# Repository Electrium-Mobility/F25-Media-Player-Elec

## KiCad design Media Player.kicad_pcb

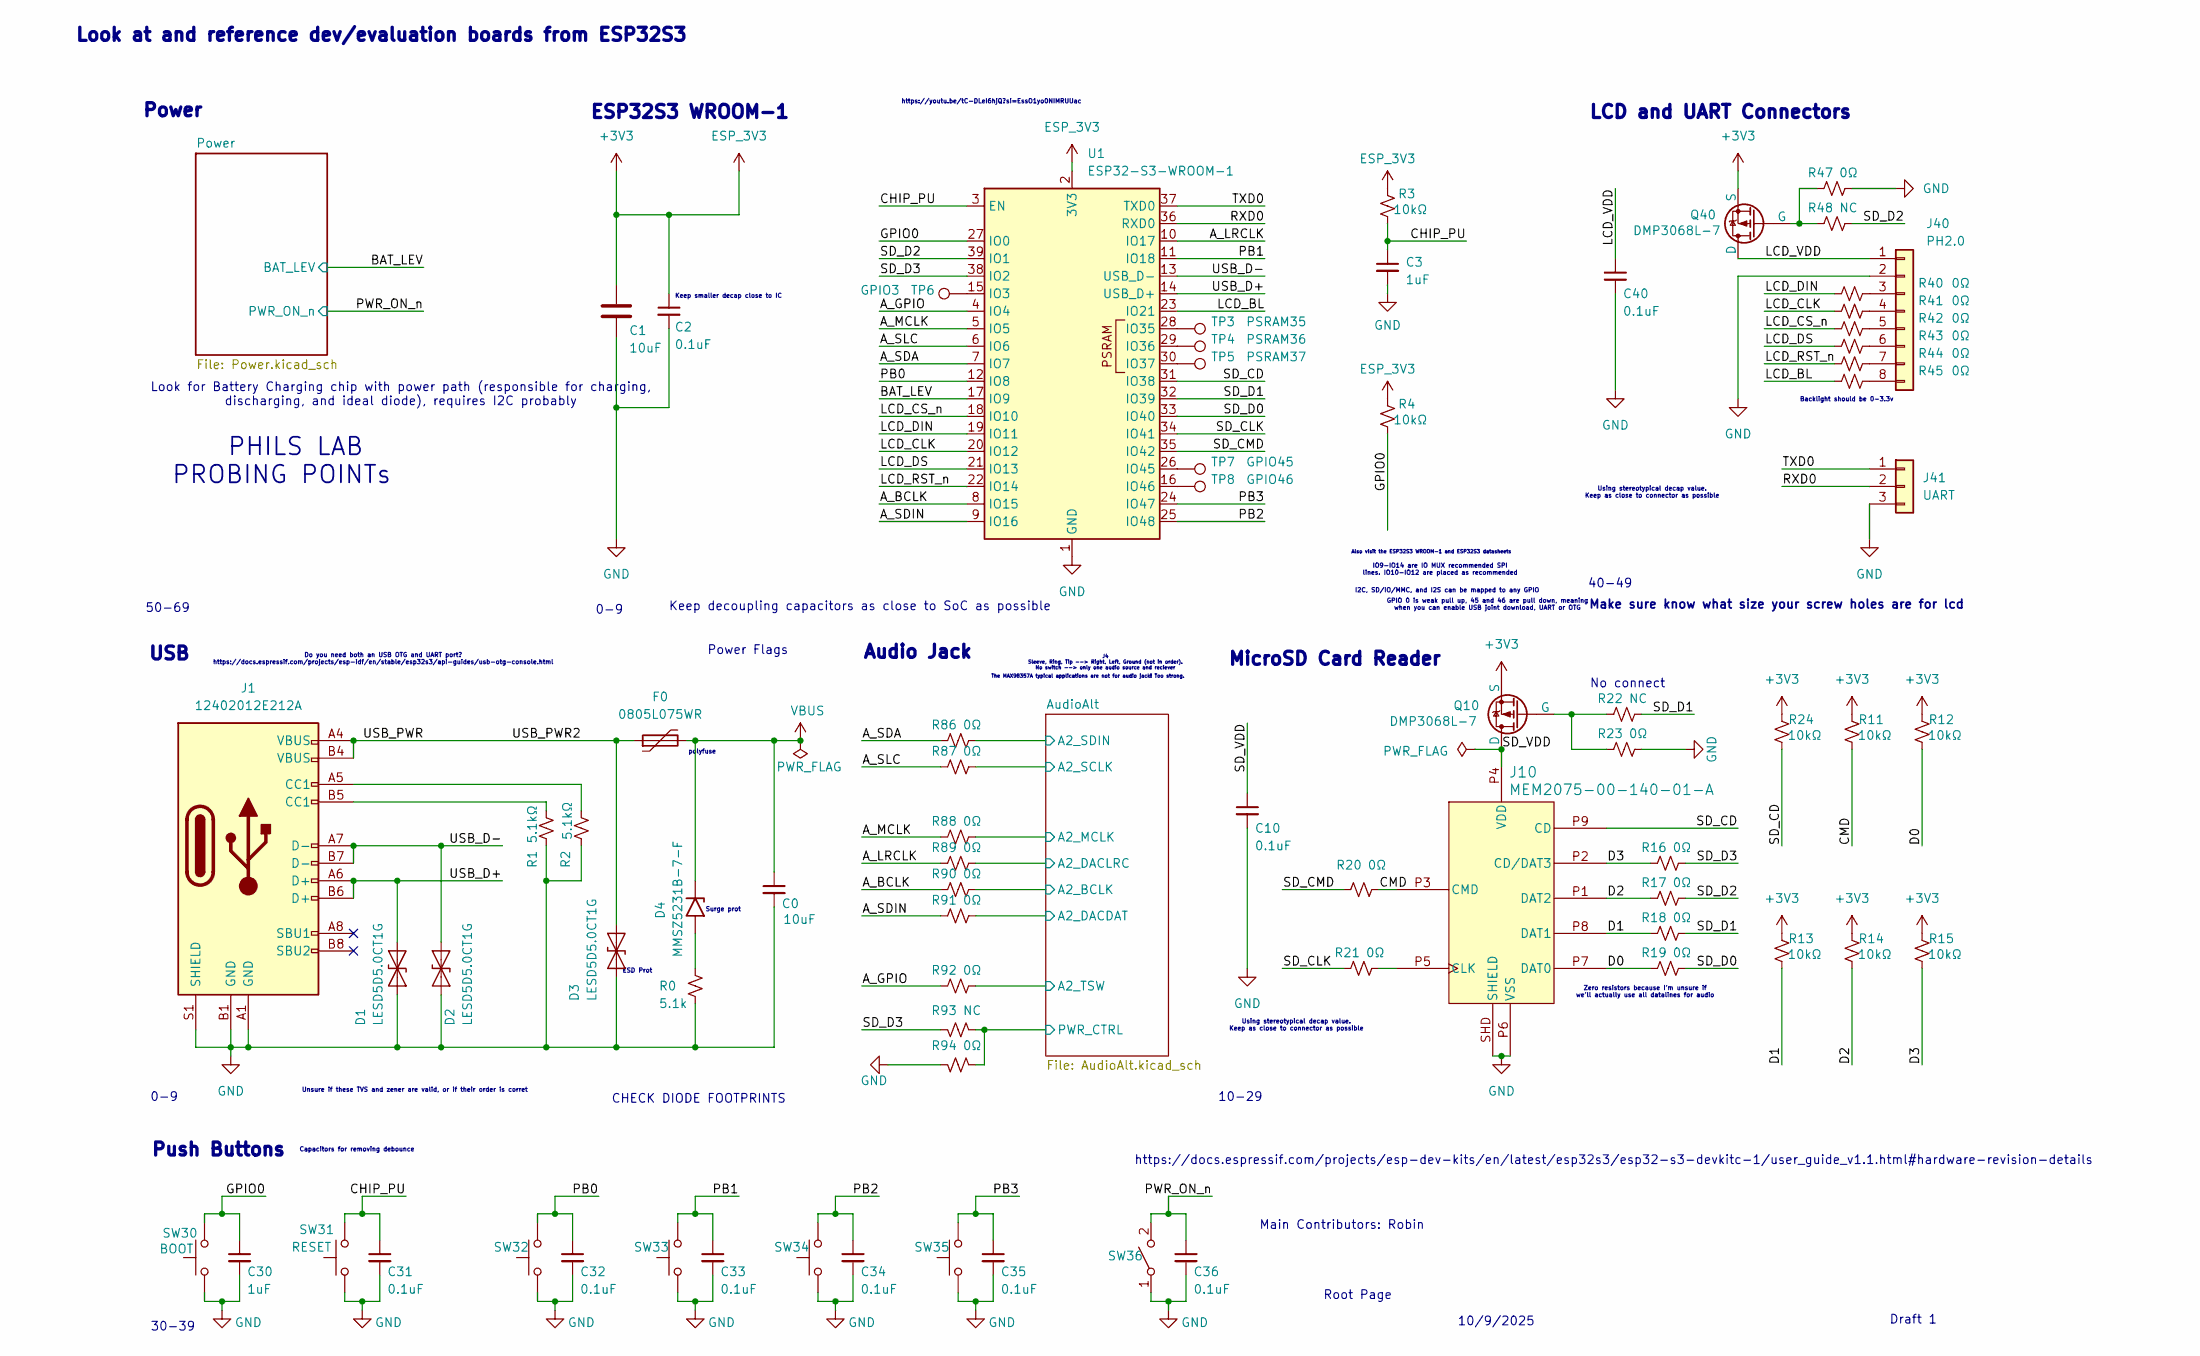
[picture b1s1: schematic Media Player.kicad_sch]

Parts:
C0: 10uF; C_0805_2012Metric_Pad1.18x1.45mm_HandSolder
C1: 10uF; C_0603_1608Metric_Pad1.08x0.95mm_HandSolder
C2, C10, C31, C32, C33, C34, C35, C36, C40: 0.1uF; C_0603_1608Metric_Pad1.08x0.95mm_HandSolder
C3, C30: 1uF; C_0603_1608Metric_Pad1.08x0.95mm_HandSolder
D1, D2, D3: LESD5D5.0CT1G; D_SOD-523
D4: MMSZ5231B-7-F; D_SOD-323
F0: 0805L075WR; D_0805_2012Metric_Pad1.15x1.40mm_HandSolder
J1: 12402012E212A; USB_C_12402012E212A_AMP
J10: MEM2075-00-140-01-A; MEM2075-00-140-01-A_GCT
J40: PH2.0; JST_EH_B8B-EH-A_1x08_P2.50mm_Vertical
J41: UART; JST_PH_B3B-PH-K_1x03_P2.00mm_Vertical
Q10, Q40: DMP3068L-7; SOT-23-3
R0: 5.1k; R_0603_1608Metric_Pad0.98x0.95mm_HandSolder
R1, R2: 5.1kΩ; R_0603_1608Metric_Pad0.98x0.95mm_HandSolder
R3, R4, R11, R12, R13, R14, R15, R24: 10kΩ; R_0603_1608Metric_Pad0.98x0.95mm_HandSolder
R16, R17, R18, R19, R20, R21, R23, R40, R41, R42, R43, R44, R45, R47, R86, R87, R88, R89, R90, R91, R92, R94: 0Ω; R_0603_1608Metric_Pad0.98x0.95mm_HandSolder
R22, R48, R93: NC; R_0603_1608Metric_Pad0.98x0.95mm_HandSolder
SW30: BOOT; SW_Push_1P1T_NO_CK_KSC6xxG
SW31: RESET; SW_Push_1P1T_NO_CK_KSC6xxG
SW32, SW33, SW34, SW35: SW_Push; SW_Push_1P1T_NO_CK_KSC6xxG
SW36: SW_SPST; SW_DIP_SPSTx01_Slide_6.7x4.1mm_W8.61mm_P2.54mm_LowProfile
TP3: PSRAM35; TestPoint_Pad_1.5x1.5mm
TP4: PSRAM36; TestPoint_Pad_1.5x1.5mm
TP5: PSRAM37; TestPoint_Pad_1.5x1.5mm
TP6: GPIO3; TestPoint_Pad_1.5x1.5mm
TP7: GPIO45; TestPoint_Pad_1.5x1.5mm
TP8: GPIO46; TestPoint_Pad_1.5x1.5mm
U1: ESP32-S3-WROOM-1

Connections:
+3V3: C1.1, C2.1, Q10.3 (S), Q40.3 (S), R3.2, R4.2, R11.2, R12.2, R13.2, R14.2, R15.2, R24.2, U1.2 (3V3); also elsewhere on the board
/A_BCLK: R90.1, U1.8 (IO15)
/A_GPIO: R92.1, U1.4 (IO4)
/A_LRCLK: R89.1, U1.10 (IO17)
/A_MCLK: R88.1, U1.5 (IO5)
/A_SDA: R86.1, U1.7 (IO7)
/A_SDIN: R91.1, U1.9 (IO16)
/A_SLC: R87.1, U1.6 (IO6)
/AudioAlt/A2_BCLK: R90.2; also elsewhere on the board
/AudioAlt/A2_DACDAT: R91.2; also elsewhere on the board
/AudioAlt/A2_DACLRC: R89.2; also elsewhere on the board
/AudioAlt/A2_MCLK: R88.2; also elsewhere on the board
/AudioAlt/A2_SCLK: R87.2; also elsewhere on the board
/AudioAlt/A2_SDIN: R86.2; also elsewhere on the board
/AudioAlt/A2_TSW: R92.2; also elsewhere on the board
/AudioAlt/PWR_CTRL: R93.1, R94.1; also elsewhere on the board
/BAT_LEV: U1.17 (IO9); also elsewhere on the board
/CHIP_PU: C3.1, C31.1, R3.1, SW31.2, U1.3 (EN)
/CMD: J10.P3 (CMD), R11.1, R20.2
/D0: J10.P7 (DAT0), R12.1, R19.1
/D1: J10.P8 (DAT1), R13.1, R18.1
/D2: J10.P1 (DAT2), R14.1, R17.1
/D3: J10.P2 (CD/DAT3), R15.1, R16.1
/GPIO0: C30.1, R4.1, SW30.2, U1.27 (IO0)
/LCD_BL: R45.1, U1.23 (IO21)
/LCD_CLK: R41.1, U1.20 (IO12)
/LCD_CS_n: R42.1, U1.18 (IO10)
/LCD_DIN: R40.1, U1.19 (IO11)
/LCD_DS: R43.1, U1.21 (IO13)
/LCD_RST_n: R44.1, U1.22 (IO14)
/LCD_VDD: C40.1, J40.1, Q40.1 (D)
/PB0: C32.1, SW32.2, U1.12 (IO8)
/PB1: C33.1, SW33.2, U1.11 (IO18)
/PB2: C34.1, SW34.2, U1.25 (IO48)
/PB3: C35.1, SW35.2, U1.24 (IO47)
/PWR_ON_n: C36.1, SW36.2 (B); also elsewhere on the board
/RXD0: J41.2, U1.36 (RXD0)
/SD_CD: J10.P9 (CD), R24.1, U1.31 (IO38)
/SD_CLK: R21.1, U1.34 (IO41)
/SD_CMD: R20.1, U1.35 (IO42)
/SD_D0: R19.2, U1.33 (IO40)
/SD_D1: R18.2, R22.2, U1.32 (IO39)
/SD_D2: R17.2, R48.2, U1.39 (IO1)
/SD_D3: R16.2, R93.2, U1.38 (IO2)
/SD_VDD: C10.1, J10.P4 (VDD), Q10.1 (D)
/TXD0: J41.1, U1.37 (TXD0)
/USB_D+: D1.1 (A1), J1.A6 (D+), J1.B6 (D+), U1.14 (USB_D+)
/USB_D-: D2.1 (A1), J1.A7 (D-), J1.B7 (D-), U1.13 (USB_D-)
/USB_PWR: D3.1 (A1), F0.1, J1.A4 (VBUS), J1.A9 (VBUS), J1.B4 (VBUS), J1.B9 (VBUS)
GND: C0.2, C1.2, C2.2, C3.2, C10.2, C30.2, C31.2, C32.2, C33.2, C34.2, C35.2, C36.2, C40.2, D1.2 (A2), D2.2 (A2), D3.2 (A2), J1.A1 (GND), J1.A12 (GND), J1.B1 (GND), J1.B12 (GND), J1.S1 (SHIELD), J10.P6 (VSS), J10.SHD (SHIELD), J40.2, J41.3, R0.2, R1.2, R2.2, R23.2, R47.2, R94.2, SW30.1, SW31.1, SW32.1, SW33.1, SW34.1, SW35.1, SW36.1 (A), U1.1 (GND), U1.40 (GND), U1.41 (GND); also elsewhere on the board
unnamed: D4.2 (A2), R0.1
unnamed: J1.A5 (CC1), R2.1
unnamed: J1.B5 (CC1), R1.1
unnamed: J10.P5 (CLK), R21.2
unnamed: J40.3, R40.2
unnamed: J40.4, R41.2
unnamed: J40.5, R42.2
unnamed: J40.6, R43.2
unnamed: J40.7, R44.2
unnamed: J40.8, R45.2
unnamed: Q10.2 (G), R22.1, R23.1
unnamed: Q40.2 (G), R47.1, R48.1
unnamed: TP6.1, U1.15 (IO3)
unnamed: TP3.1, U1.28 (IO35)
unnamed: TP4.1, U1.29 (IO36)
unnamed: TP5.1, U1.30 (IO37)
unnamed: TP7.1, U1.26 (IO45)
unnamed: TP8.1, U1.16 (IO46)
VBUS: C0.1, D4.1 (A1), F0.2; also elsewhere on the board

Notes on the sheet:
LCD and UART Connectors
Look for Battery Charging chip with power path (responsible for charging, discharging, and ideal diode), requires I2C probably
Keep decoupling capacitors as close to SoC as possible
50-69
ESP32S3 WROOM-1
Capacitors for removing debounce
Look at and reference dev/evaluation boards from ESP32S3
IO9-IO14 are IO MUX recommended SPI lines. IO10-IO12 are placed as recommended
Make sure know what size your screw holes are for lcd
GPIO 0 is weak pull up, 45 and 46 are pull down, meaning when you can enable USB joint download, UART or OTG
Push Buttons
Using stereotypical decap value. Keep as close to connector as possible
MicroSD Card Reader
Backlight should be 0-3.3v
0-9
I2C, SD/IO/MMC, and I2S can be mapped to any GPIO
Surge prot
10/9/2025
Root Page
Zero resistors because I'm unsure if we'll actually use all datalines for audio
10-29
Unsure if these TVS and zener are valid, or if their order is corret
CHECK DIODE FOOTPRINTS
Power
polyfuse
40-49
Audio Jack
30-39
Do you need both an USB OTG and UART port? https://docs.espressif.com/projects/esp-idf/en/stable/esp32s3/api-guides/usb-otg-console.html
PROBING POINTs
The MAX98357A typical applications are not for audio jack! Too strong.
Also visit the ESP32S3 WROOM-1 and ESP32S3 datasheets
Keep smaller decap close to IC
Main Contributors: Robin
No connect
PHILS LAB
Draft 1
ESD Prot
USB
https://docs.espressif.com/projects/esp-dev-kits/en/latest/esp32s3/esp32-s3-devkitc-1/user_guide_v1.1.html#hardware-revision-details

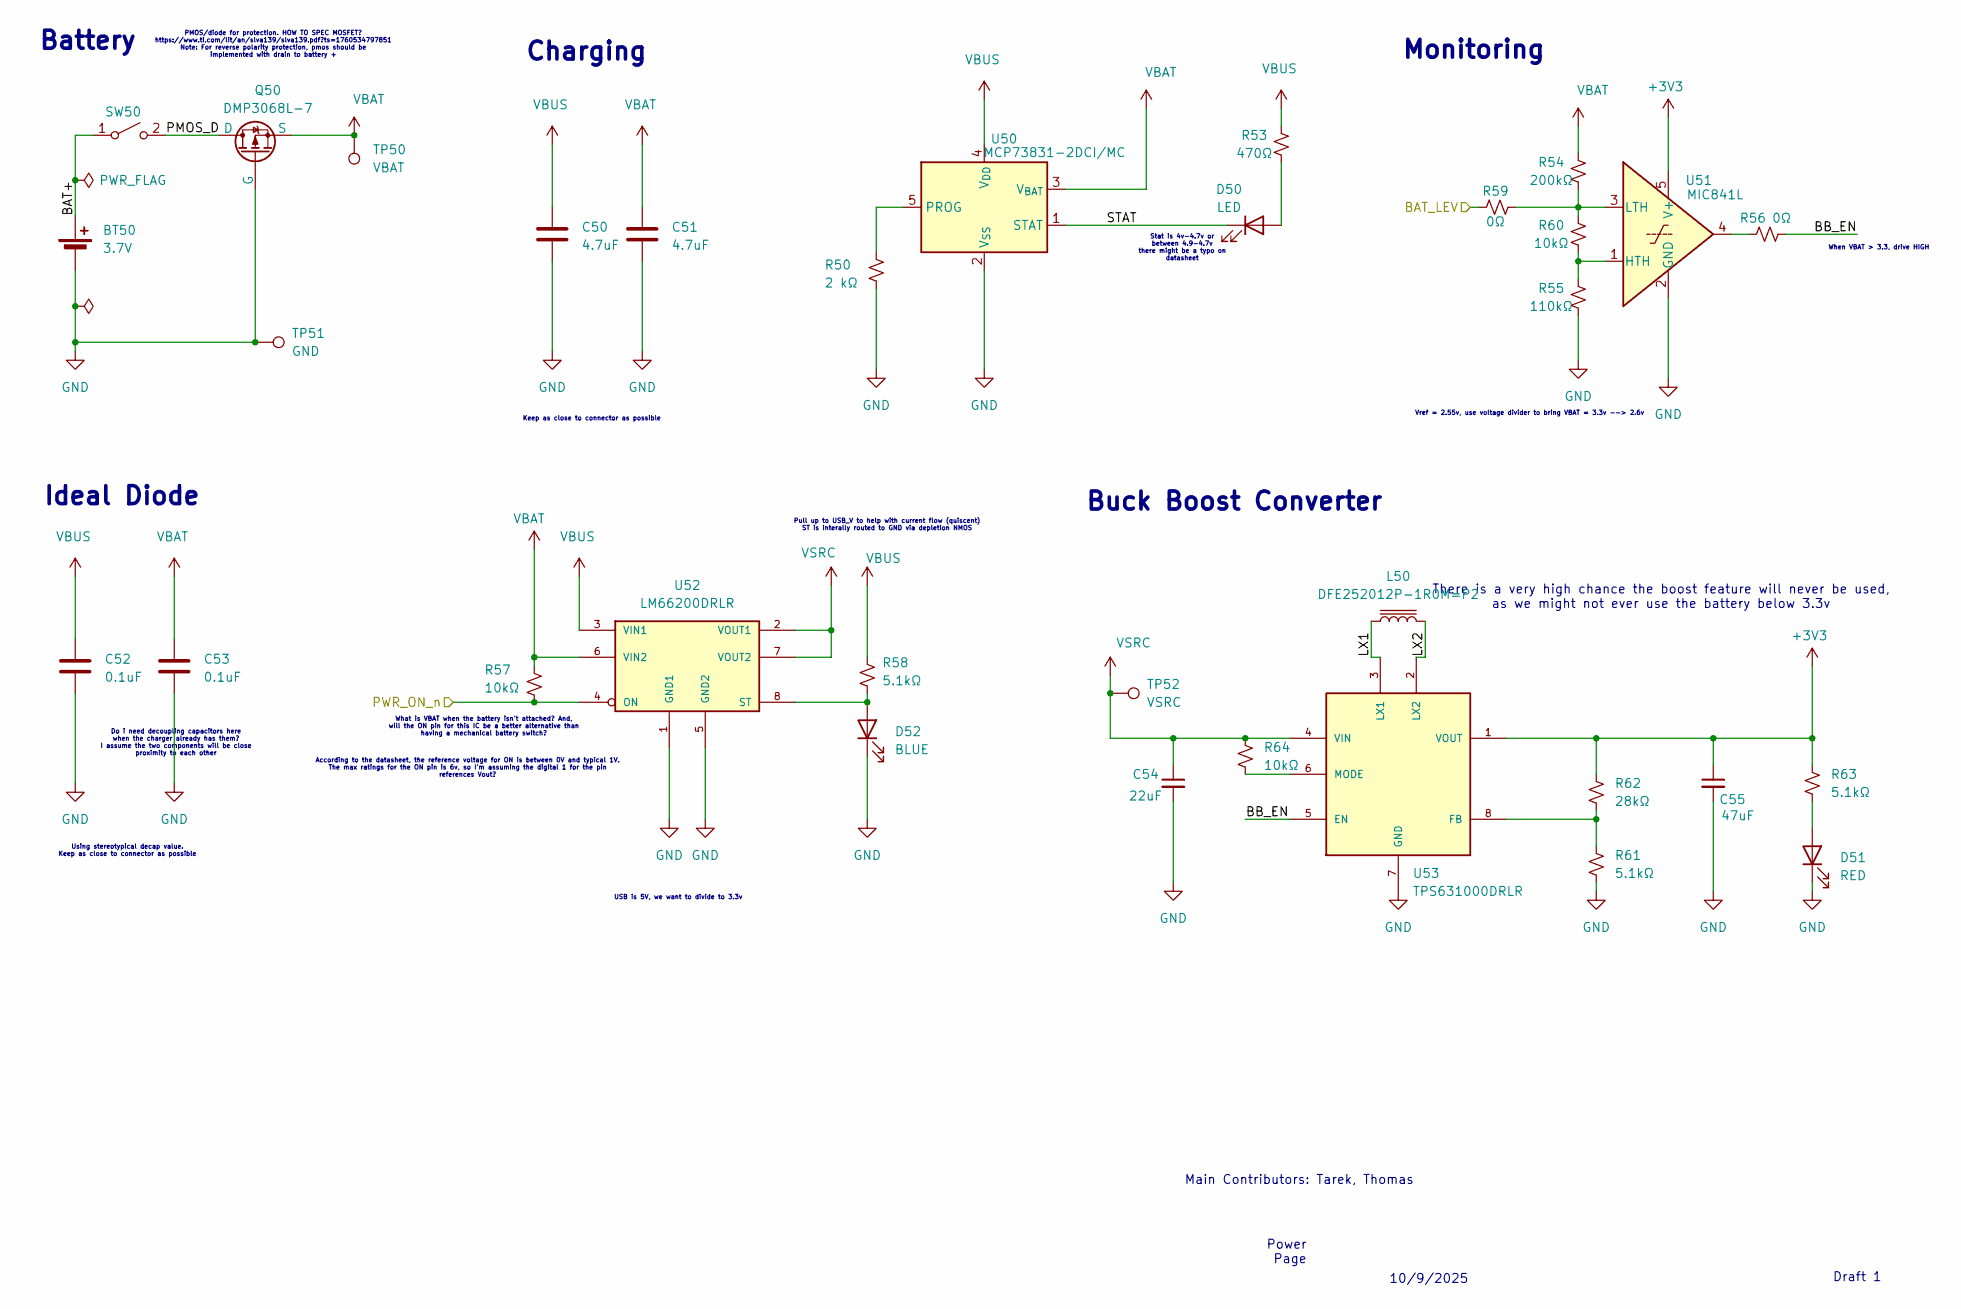
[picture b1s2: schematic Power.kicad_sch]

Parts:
BT50: 3.7V; JST_PH_B2B-PH-K_1x02_P2.00mm_Vertical
C50, C51: 4.7uF; C_0603_1608Metric_Pad1.08x0.95mm_HandSolder
C52, C53: 0.1uF; C_0603_1608Metric_Pad1.08x0.95mm_HandSolder
C54: 22uF; C_0805_2012Metric
C55: 47uF; C_0805_2012Metric
D50: LED; LED_0603_1608Metric
D51: RED; LED_0603_1608Metric
D52: BLUE; LED_0603_1608Metric
L50: DFE252012P-1R0M=P2; L_1008_2520Metric
Q50: DMP3068L-7; SOT-23-3
R50: 2 kΩ; R_0603_1608Metric_Pad0.98x0.95mm_HandSolder
R53: 470Ω; R_0603_1608Metric_Pad0.98x0.95mm_HandSolder
R54: 200kΩ; R_0603_1608Metric_Pad0.98x0.95mm_HandSolder
R55: 110kΩ; R_0603_1608Metric_Pad0.98x0.95mm_HandSolder
R56, R59: 0Ω; R_0603_1608Metric_Pad0.98x0.95mm_HandSolder
R57, R60, R64: 10kΩ; R_0603_1608Metric_Pad0.98x0.95mm_HandSolder
R58, R61, R63: 5.1kΩ; R_0603_1608Metric_Pad0.98x0.95mm_HandSolder
R62: 28kΩ; R_0603_1608Metric_Pad0.98x0.95mm_HandSolder
SW50: SW_SPST; SW_DIP_SPSTx01_Slide_6.7x4.1mm_W8.61mm_P2.54mm_LowProfile
TP50: VBAT; TestPoint_Pad_1.5x1.5mm
TP51: GND; TestPoint_THTPad_1.5x1.5mm_Drill0.7mm
TP52: VSRC; TestPoint_Pad_1.5x1.5mm
U50: MCP73831-2DCI/MC; SOT-23-5
U51: MIC841L; SOT-353_SC-70-5
U52: LM66200DRLR; SOT-583-8
U53: TPS631000DRLR; SOT-583-8; PARTREV B

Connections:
+3V3: C55.1, R62.1, R63.1, U51.5 (V+), U53.1 (VOUT); also elsewhere on the board
/BAT_LEV: R59.2; also elsewhere on the board
/PWR_ON_n: R57.2, U52.4 (ON); also elsewhere on the board
/Power/BAT+: BT50.1 (+), SW50.1 (A)
/Power/BB_EN: R56.2, U53.5 (EN)
/Power/LX1: L50.1, U53.3 (LX1)
/Power/LX2: L50.2, U53.2 (LX2)
/Power/PMOS_D: Q50.1 (D), SW50.2 (B)
/Power/STAT: D50.1 (K), U50.1 (STAT)
GND: BT50.2 (-), C50.1, C51.1, C52.1, C53.1, C54.2, C55.2, D51.1 (K), D52.1 (K), Q50.2 (G), R50.2, R55.1, R61.2, TP51.1, U50.2 (V_{SS}), U51.2 (GND), U52.1 (GND1), U52.5 (GND2), U53.7 (GND); also elsewhere on the board
unnamed: D50.2 (A), R53.1
unnamed: D51.2 (A), R63.2
unnamed: D52.2 (A), R58.2, U52.8 (ST)
unnamed: R56.1, U51.4
unnamed: R50.1, U50.5 (PROG)
unnamed: R55.2, R60.1, U51.1 (HTH)
unnamed: R54.1, R59.1, R60.2, U51.3 (LTH)
unnamed: R61.1, R62.2, U53.8 (FB)
unnamed: R64.2, U53.6 (MODE)
VBAT: C51.2, C53.2, Q50.3 (S), R54.2, R57.1, TP50.1, U50.3 (V_{BAT}), U52.6 (VIN2)
VBUS: C50.2, C52.2, R53.2, R58.1, U50.4 (V_{DD}), U52.3 (VIN1); also elsewhere on the board
VSRC: C54.1, R64.1, TP52.1, U52.2 (VOUT1), U52.7 (VOUT2), U53.4 (VIN)

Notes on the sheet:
Pull up to USB_V to help with current flow (quiscent) ST is interally routed to GND via depletion NMOS
Power Page
Vref = 2.55v, use voltage divider to bring VBAT = 3.3v --> 2.6v
Do i need decoupling capacitors here when the charger already has them? I assume the two components will be close proximity to each other
According to the datasheet, the reference voltage for ON is between 0V and typical 1V. The max ratings for the ON pin is 6v, so I'm assuming the digital 1 for the pin references Vout?
What is VBAT when the battery isn't attached? And, will the ON pin for this IC be a better alternative than having a mechanical battery switch?
Keep as close to connector as possible
Charging
Main Contributors: Tarek, Thomas
Battery
10/9/2025
There is a very high chance the boost feature will never be used, as we might not ever use the battery below 3.3v
When VBAT > 3.3, drive HIGH
Ideal Diode
Using stereotypical decap value. Keep as close to connector as possible
Buck Boost Converter
Draft 1
USB is 5V, we want to divide to 3.3v
Monitoring
PMOS/diode for protection. HOW TO SPEC MOSFET? https://www.ti.com/lit/an/slva139/slva139.pdf?ts=1760534797851 Note: For reverse polarity protection, pmos should be implemented with drain to battery +
Stat is 4v-4.7v or between 4.9-4.7v there might be a typo on datasheet

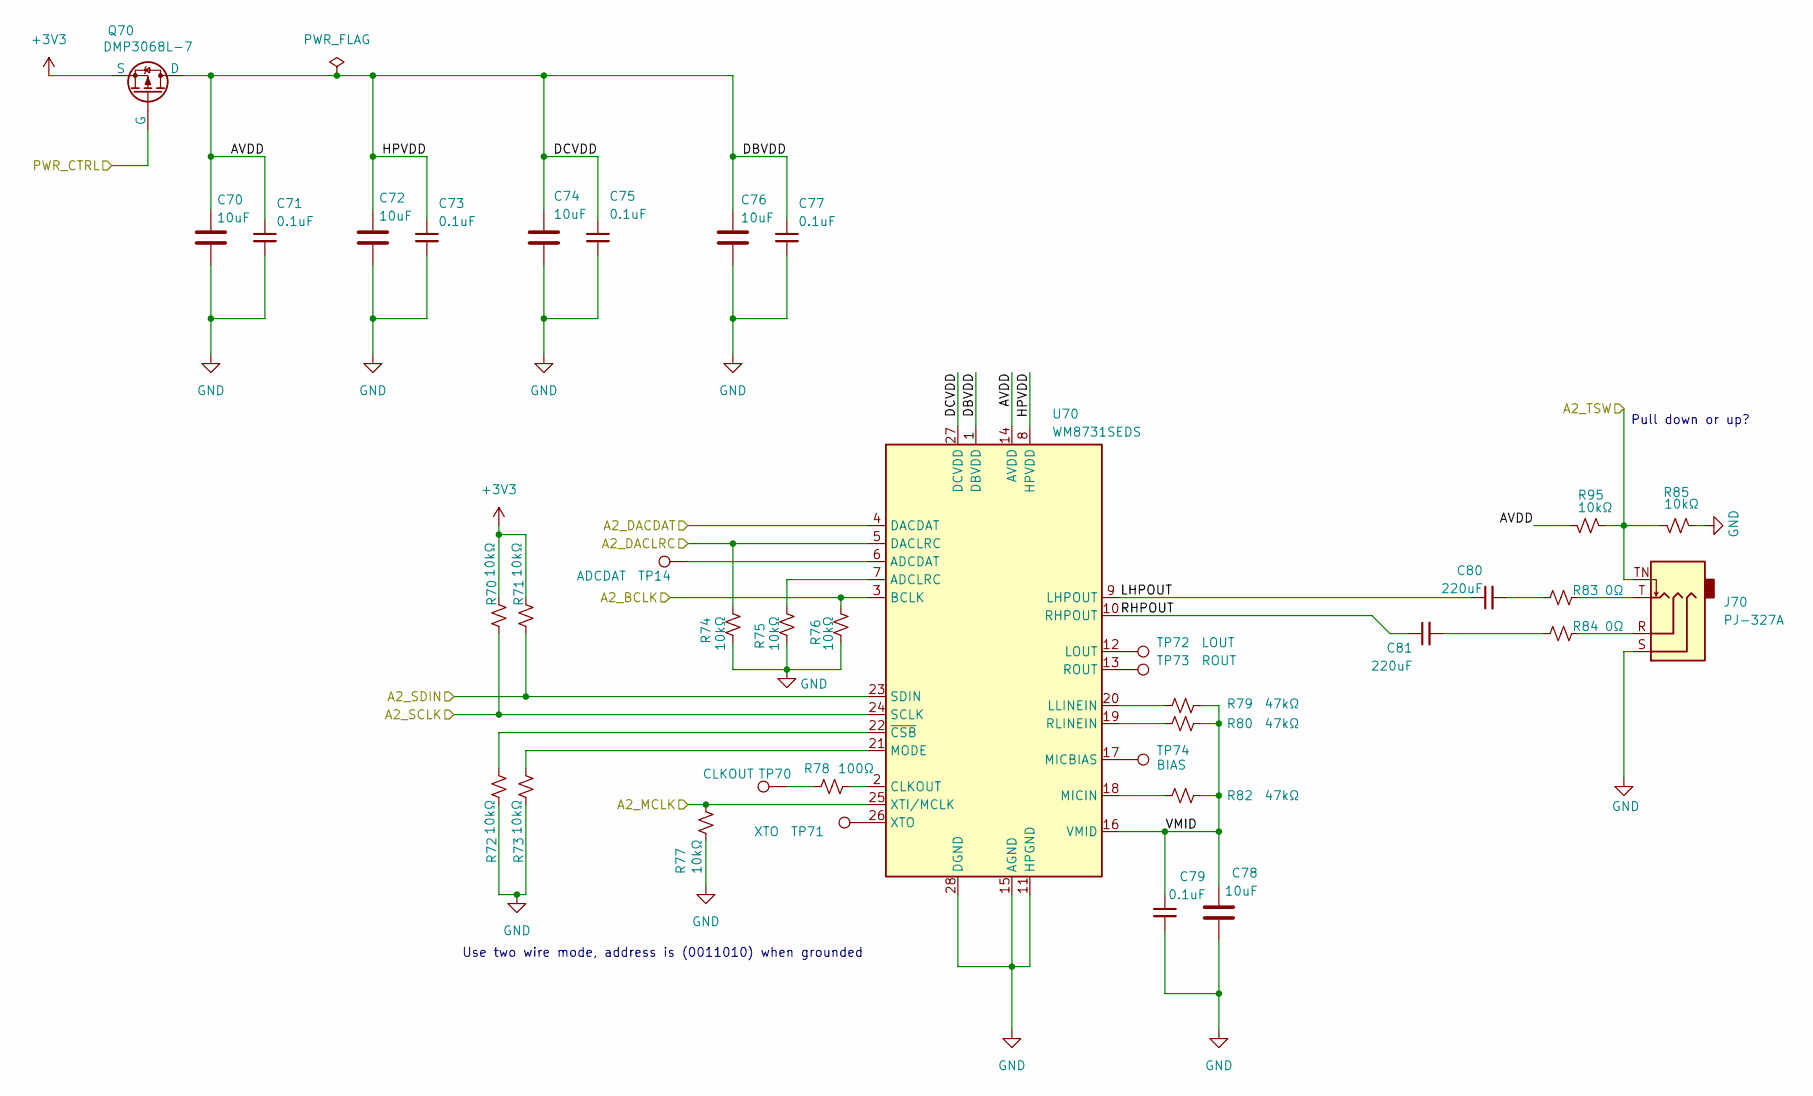
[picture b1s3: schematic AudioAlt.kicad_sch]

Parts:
C70, C72, C74, C76, C78: 10uF; C_0603_1608Metric_Pad1.08x0.95mm_HandSolder
C71, C73, C75, C77, C79: 0.1uF; C_0603_1608Metric_Pad1.08x0.95mm_HandSolder
C80, C81: 220uF; C_0603_1608Metric_Pad1.08x0.95mm_HandSolder
J70: PJ-327A; Korean Hroparts Elec PJ-327C-4A
Q70: DMP3068L-7; SOT-23-3
R70, R71, R72, R73, R74, R75, R76, R77, R85, R95: 10kΩ; R_0603_1608Metric_Pad0.98x0.95mm_HandSolder
R78: 100Ω; R_0603_1608Metric_Pad0.98x0.95mm_HandSolder
R79, R80, R82: 47kΩ; R_0603_1608Metric_Pad0.98x0.95mm_HandSolder
R83, R84: 0Ω; R_0603_1608Metric_Pad0.98x0.95mm_HandSolder
TP14: ADCDAT; TestPoint_Pad_1.5x1.5mm
TP70: CLKOUT; TestPoint_Pad_1.5x1.5mm
TP71: XTO; TestPoint_Pad_1.5x1.5mm
TP72: LOUT; TestPoint_Pad_1.5x1.5mm
TP73: ROUT; TestPoint_Pad_1.5x1.5mm
TP74: BIAS; TestPoint_Pad_1.5x1.5mm
U70: WM8731SEDS; SSOP-28_5.3x10.2mm_P0.65mm

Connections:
+3V3: Q70.3 (S), R70.1, R71.1; also elsewhere on the board
/AudioAlt/A2_BCLK: R76.1, U70.3 (BCLK); also elsewhere on the board
/AudioAlt/A2_DACDAT: U70.4 (DACDAT); also elsewhere on the board
/AudioAlt/A2_DACLRC: R74.1, U70.5 (DACLRC); also elsewhere on the board
/AudioAlt/A2_MCLK: R77.1, U70.25 (XTI/MCLK); also elsewhere on the board
/AudioAlt/A2_SCLK: R70.2, U70.24 (SCLK); also elsewhere on the board
/AudioAlt/A2_SDIN: R71.2, U70.23 (SDIN); also elsewhere on the board
/AudioAlt/A2_TSW: J70.TN, R85.1, R95.2; also elsewhere on the board
/AudioAlt/AVDD: C70.1, C71.1, C72.1, C73.1, C74.1, C75.1, C76.1, C77.1, Q70.1 (D), R95.1, U70.1 (DBVDD), U70.8 (HPVDD), U70.14 (AVDD), U70.27 (DCVDD)
/AudioAlt/LHPOUT: C80.1, U70.9 (LHPOUT)
/AudioAlt/PWR_CTRL: Q70.2 (G); also elsewhere on the board
/AudioAlt/RHPOUT: C81.1, U70.10 (RHPOUT)
/AudioAlt/VMID: C78.1, C79.1, R79.1, R80.1, R82.1, U70.16 (VMID)
GND: C70.2, C71.2, C72.2, C73.2, C74.2, C75.2, C76.2, C77.2, C78.2, C79.2, J70.S, R72.2, R73.2, R74.2, R75.2, R76.2, R77.2, R85.2, U70.11 (HPGND), U70.15 (AGND), U70.28 (DGND); also elsewhere on the board
unnamed: C80.2, R83.1
unnamed: C81.2, R84.1
unnamed: J70.R, R84.2
unnamed: J70.T, R83.2
unnamed: R78.2, TP70.1
unnamed: TP14.1, U70.6 (ADCDAT)
unnamed: R75.1, U70.7 (ADCLRC)
unnamed: R78.1, U70.2 (CLKOUT)
unnamed: R79.2, U70.20 (LLINEIN)
unnamed: TP72.1, U70.12 (LOUT)
unnamed: TP74.1, U70.17 (MICBIAS)
unnamed: R82.2, U70.18 (MICIN)
unnamed: R73.1, U70.21 (MODE)
unnamed: R80.2, U70.19 (RLINEIN)
unnamed: TP73.1, U70.13 (ROUT)
unnamed: TP71.1, U70.26 (XTO)
unnamed: R72.1, U70.22 (~CSB)

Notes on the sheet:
Use two wire mode, address is (0011010) when grounded
Pull down or up?

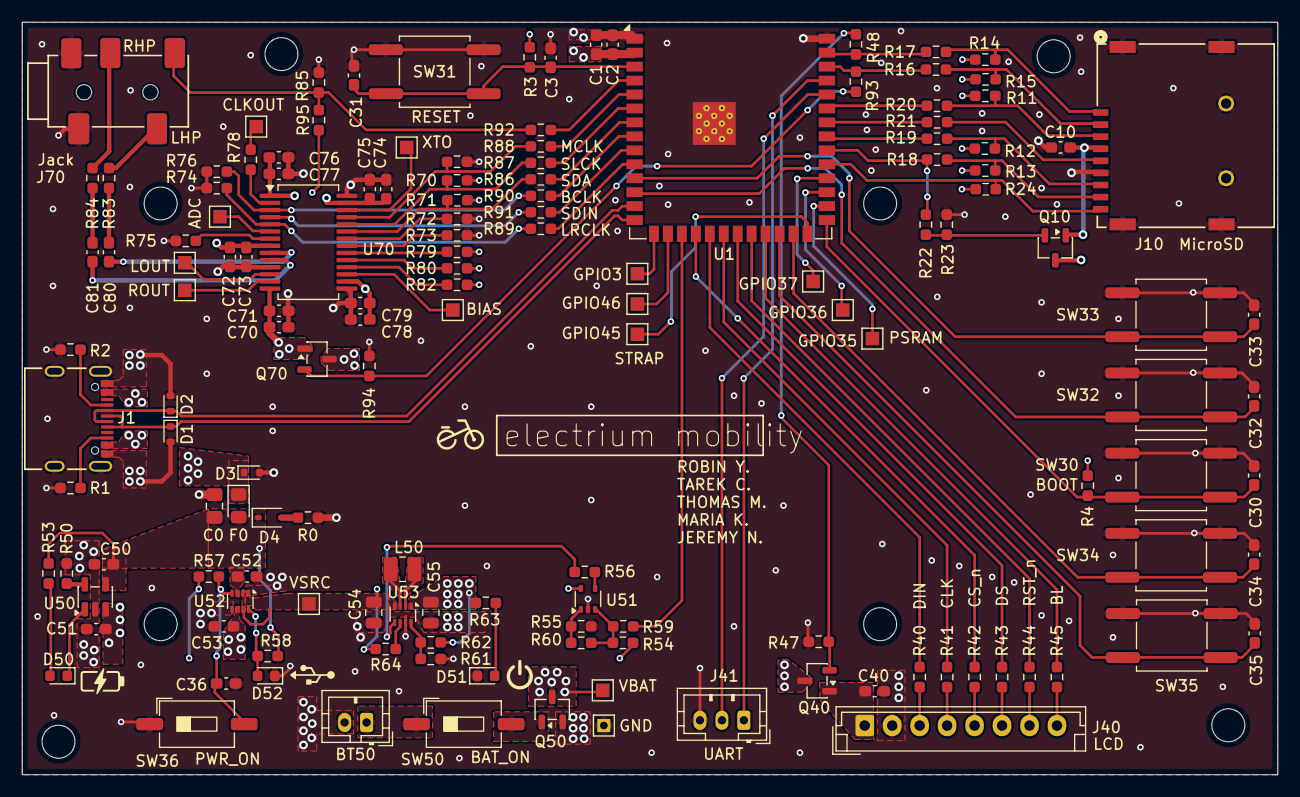
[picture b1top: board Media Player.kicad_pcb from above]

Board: 4 copper layers, 114.3 x 68.5 mm, 144 parts (0 on the bottom side), 107 nets.

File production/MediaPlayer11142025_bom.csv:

Designator,Footprint,Quantity,Value,LCSC Part #
BT50,JST_PH_B2B-PH-K_1x02_P2.00mm_Vertical,1,3.7V,
C0,0805,1,10uF,
"C1, C70, C72, C74, C76, C78",0603,6,10uF,
"C10, C2, C31, C32, C33, C34, C35, C36, C40, C52, C53, C71, C73, C75, C77, C79",0603,16,0.1uF,
"C3, C30",0603,2,1uF,
"C50, C51",0603,2,4.7uF,
C54,0805,1,22uF,
C55,0805,1,47uF,
"C80, C81",0603,2,220uF,
"D1, D2, D3",D_SOD-523,3,LESD5D5.0CT1G,
D4,D_SOD-323,1,MMSZ5231B-7-F,
D50,0603,1,LED,
D51,0603,1,RED,
D52,0603,1,BLUE,
F0,0805,1,0805L075WR,
J1,USB_C_12402012E212A_AMP,1,12402012E212A,
J10,MEM2075-00-140-01-A_GCT,1,MEM2075-00-140-01-A,
J40,JST_EH_B8B-EH-A_1x08_P2.50mm_Vertical,1,PH2.0,
J41,JST_PH_B3B-PH-K_1x03_P2.00mm_Vertical,1,UART,
J70,Korean Hroparts Elec PJ-327C-4A,1,PJ-327A,
L50,1008,1,DFE252012P-1R0M=P2,
"Q10, Q40, Q50, Q70",SOT-23-3,4,DMP3068L-7,
R0,0603,1,5.1k,
"R1, R2, R58, R61, R63",0603,5,5.1kΩ,
"R11, R12, R13, R14, R15, R24, R3, R4, R57, R60, R64, R70, R71, R72, R73, R74, R75, R76, R77, R85, R95",0603,21,10kΩ,
"R16, R17, R18, R19, R20, R21, R23, R40, R41, R42, R43, R44, R45, R47, R56, R59, R83, R84, R86, R87, R88, R89, R90, R91, R92, R94",0603,26,0Ω,
"R22, R48, R93",0603,3,NC,
R50,0603,1,2 kΩ,
R53,0603,1,470Ω,
R54,0603,1,200kΩ,
R55,0603,1,110kΩ,
R62,0603,1,28kΩ,
R78,0603,1,100Ω,
"R79, R80, R82",0603,3,47kΩ,
SW30,SW_Push_1P1T_NO_CK_KSC6xxG,1,BOOT,
SW31,SW_Push_1P1T_NO_CK_KSC6xxG,1,RESET,
"SW32, SW33, SW34, SW35",SW_Push_1P1T_NO_CK_KSC6xxG,4,SW_Push,
"SW36, SW50",SW_DIP_SPSTx01_Slide_6.7x4.1mm_W8.61mm_P2.54mm_LowProfile,2,SW_SPST,
TP14,TestPoint_Pad_1.5x1.5mm,1,ADCDAT,
TP3,TestPoint_Pad_1.5x1.5mm,1,PSRAM35,
TP4,TestPoint_Pad_1.5x1.5mm,1,PSRAM36,
TP5,TestPoint_Pad_1.5x1.5mm,1,PSRAM37,
TP50,TestPoint_Pad_1.5x1.5mm,1,VBAT,
TP51,TestPoint_THTPad_1.5x1.5mm_Drill0.7mm,1,GND,
TP52,TestPoint_Pad_1.5x1.5mm,1,VSRC,
TP6,TestPoint_Pad_1.5x1.5mm,1,GPIO3,
TP7,TestPoint_Pad_1.5x1.5mm,1,GPIO45,
TP70,TestPoint_Pad_1.5x1.5mm,1,CLKOUT,
TP71,TestPoint_Pad_1.5x1.5mm,1,XTO,
TP72,TestPoint_Pad_1.5x1.5mm,1,LOUT,
TP73,TestPoint_Pad_1.5x1.5mm,1,ROUT,
TP74,TestPoint_Pad_1.5x1.5mm,1,BIAS,
TP8,TestPoint_Pad_1.5x1.5mm,1,GPIO46,
U1,ESP32-S3-WROOM-1,1,ESP32-S3-WROOM-1,
U50,SOT-23-5,1,MCP73831-2DCI/MC,
U51,SOT-353_SC-70-5,1,MIC841L,
U52,SOT-583-8,1,LM66200DRLR,
U53,SOT-583-8,1,TPS631000DRLR,
U70,SSOP-28_5.3x10.2mm_P0.65mm,1,WM8731SEDS,

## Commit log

2025-10-03 Added Power sub page.
2025-10-03 Placed Major Components, No Power
    Placed ESP32S3, Connector to LCD, SD card reader, USB. Audio Jack components still tbd. Power is a hierarchical page/symbol, no pins right now.
    Note to self: KiCAD will crash if you try to edit symbols by double clicking on them inside a schematic. Use symbol editor instead.
2025-10-07 Most connections formed except component values and audio amp
2025-10-08 Changed Audio Amplifier to MAX9850
    MAX9850 is so complicated - you use I2C to set the internal registers to modify and initialize the IC before you use I2S to send audio data to DAC. You can also choose to send analog data with AC cou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
2025-10-09 Draft 1 - Main components and wiring complete
    Connections may be innacurate or violate electrical specs, or perhaps aren't set up "properly".
2025-10-09 Added missing datasheets.
2025-10-09 Added PMOS to battery + power flags
    Still missing values for a lot of components
2025-10-11 Charger
2025-10-11 with footprints
2025-10-12 Added most of the footprints needed
2025-10-13 Finished off the last footprints
2025-10-15 Draft 2: Protection circuitry and fixed I/O signals
    Still missing PMOS spec for reverse polarity battery protection. Added TVS to USB, voltage divided certain output signals from ICs into ESP GPIO. Checked some component values.
2025-10-15 Removed comment block
2025-10-17 Draft 2 Revision 2
    Footprints still not all assigned.
    Added: Test points, zero resistors, battery voltage monitor IC, PTC and zener surge protection on VBUS, UART connector
    Changed: rerouted some signals, removed zener and resistor for reverse pol bat protection
2025-10-20 Remaining Footprint Added
    Beware of footprints that come from online but do not match the kicad libraries - the pins might be mapped wrong!
2025-10-20 Components Placed on Layout
    Added Power Management PMOS, Assigned missing footprints
2025-10-20 Filtered Ratsnest
    Moved all related components into their respective groups
2025-10-24 Ratsnest organized
    Certain pins on esp32 module changed to benefit layout. Named all decaps to dC. Current layout areas might be not optimal, i.e. complicated to wire
2025-10-27 Component Re-order
2025-10-27 Added alternative audio IC
    Added a SOP package audio IC (for easier board bring up) in hopes to replace MAX9850. Pins not fully mapped yet.
2025-10-29 Board stuffing, new audio on board
    Added new Audio IC to PCB.
    Started moving everything into a estimated board size, AKA restricted area. Things seem REALL TIGHT. There's not enough space, I think I'll have to change resistor footprints
2025-10-31 Draft 1
    I'm not very fond of some of my traces. Especially the power component. Not even sure if all components are routed properly. Still missing GND and PWR plane, so most component power not routed. Missi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
2025-10-31 Temporary Commit
2025-11-01 Small Change to USB routing
    Removed 0 resistors and change components to match reference schematic
2025-11-01 Compacting part 1
2025-11-03 Compacting Part 2, Pre-Draft 2
    Compacted more parts. Organized power routing and added envisioned power plane sections. Added screw holes for board and LCD. Shrunk max board size down.
    Still need to replace the diode for surge prot as the copper pads are way too small for direction large amounts of current.
2025-11-05 JLC Design restraints
    Updated design rules with JLC PCB. Combined numbers from Phils Lab and GPT for beginner friendly values (first board)
2025-11-05 Bucked
    The Boost Buck Converter layout is from the datasheet. I'm not really sure how many via's I'll need for power since the IC is so small yet its the only source of power feeding all the other periphera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
2025-11-06 Ideal Diode
    Layout based on ds
2025-11-07 Layout Draft 2, or almost
    Charger layout based off of reference. Used more copper regions rather than traces. Other traces like buttons and test pads routed. Tried my best to make it all look good and parallel.
    Added more silkscreen and logo.
    STILL NEED TO DO POWER PLANE.
2025-11-07 Layout 2! Pre-DRC
    32 DRC errors. 116 Warnings.
    Inserted power planes. Now is time for optimization and fixing.
2025-11-08 Most DRC errors removed EXCEPT USB
    USB receptacle pins are too close to each other and the design rules I set are upset
    (31 errors, 1.9mm instead of the minimum 2.0mm)
2025-11-09 Copper Ground Pour, Traces Moved to Upper Layer
    Replaced gnd trace around D+ D- and SDIO CLK with full board GND pour. DRC issues with gnd pour right now. Also moved a lot of un-necessary back layer signal traces to top layer. DRC still somewhat u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
2025-11-11 Minor Changes
    Power traces enlarged, certain pad and hole clearances on USB modified, still within design rules, fixed silk screen clearance, copper pours now with thermal relief for pads connected to large planes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
2025-11-13 Ground Stitching, PMOS 0-Res Moved,
    DRC should be near cleared. Might want to reconsider mapping some pin functions? SD card detect line, also battery checker (making use of comparator). Also, double check if audio IC microphone pins (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
2025-11-14 UNFINISHED: Rerouted Traces, new LEDs, replaced components
    Removed charging status and power source signals from MCU and gave them their own LEDs. Added analog battery voltage and card detect as replacement. Also found out not all components are in stock... 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
2025-11-14 New Audio Jack
    Replaced audio jack with actually available component from xunpu, changed MIC845 to MIC841. Still need to double check the audio codec
2025-11-14 No changes made.
2025-11-14 ORDERED: Updated Footprints, Silk Screen, Mounting Holes
    Minor changes. This is the version sent to JLC
